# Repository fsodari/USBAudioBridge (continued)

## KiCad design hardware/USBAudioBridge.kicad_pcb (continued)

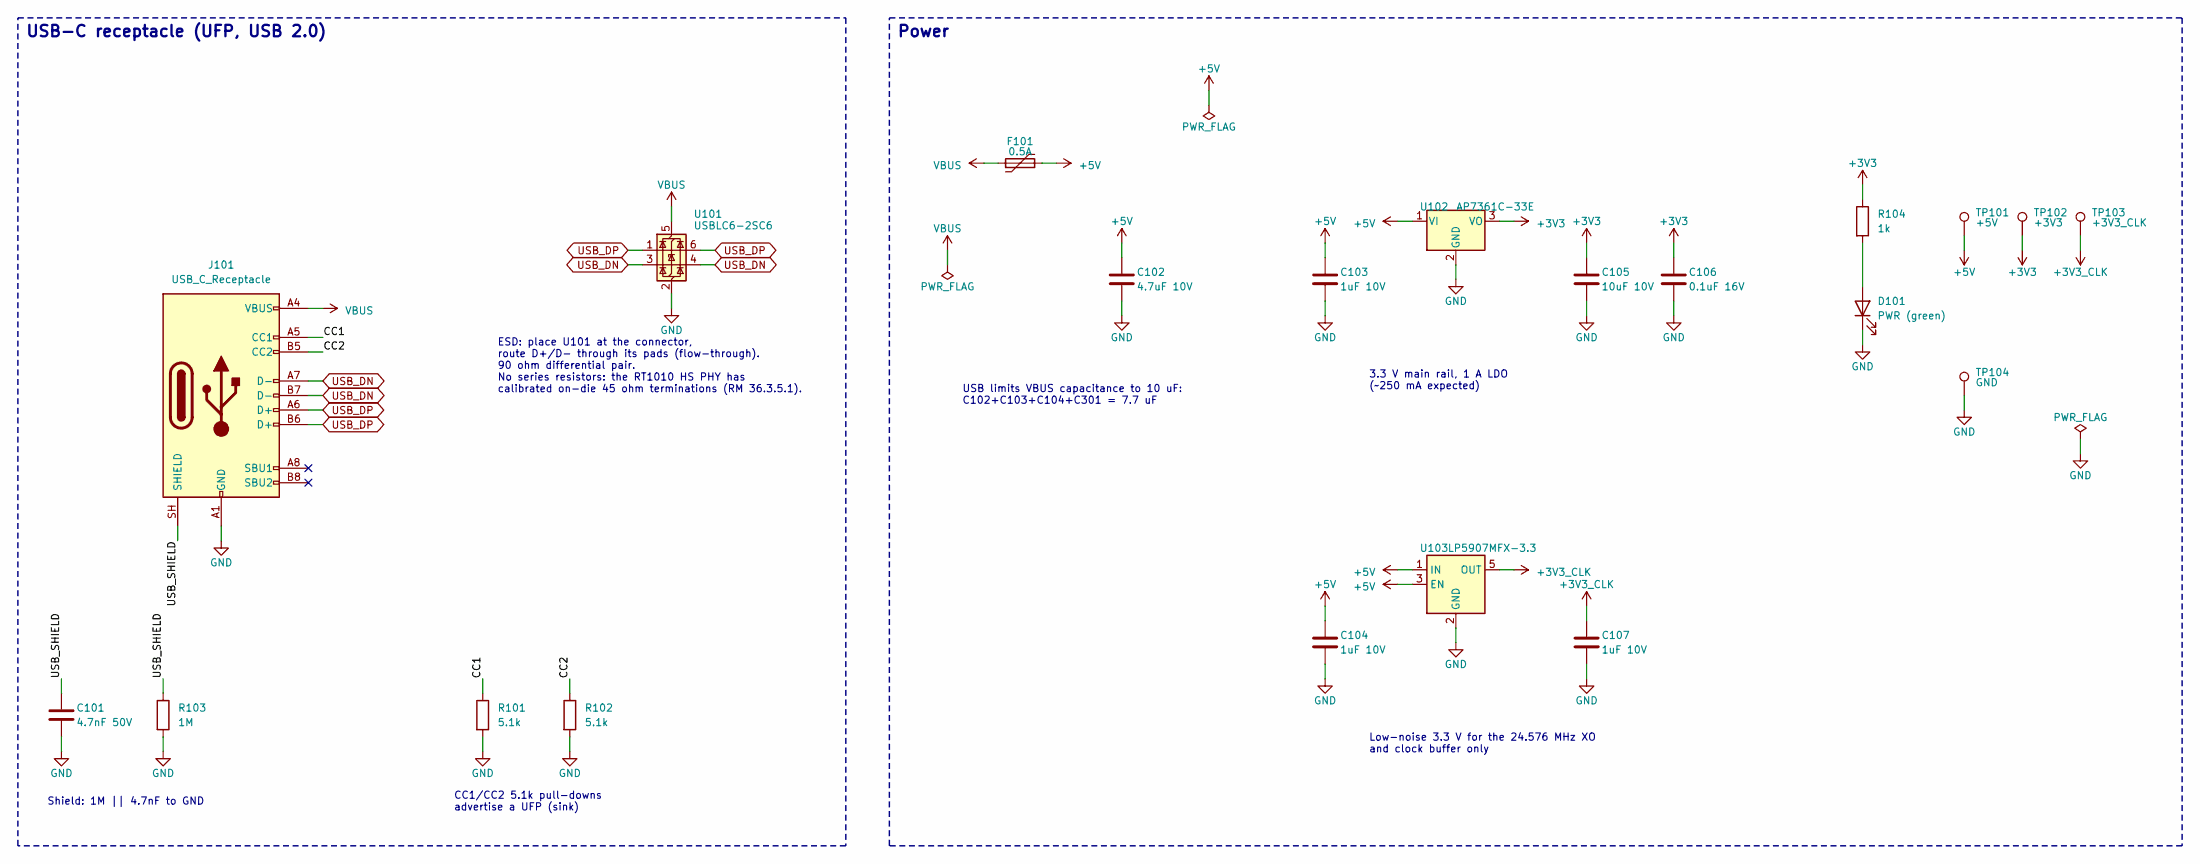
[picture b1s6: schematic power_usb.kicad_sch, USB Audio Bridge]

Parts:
C101: 4.7nF 50V; C_0402_1005Metric; MPN 0402B472K500NT; LCSC C1538
C102: 4.7uF 10V; C_0603_1608Metric; MPN CL10A475KO8NNNC; LCSC C19666
C103, C104, C107: 1uF 10V; C_0603_1608Metric; MPN CL10A105KB8NNNC; LCSC C15849
C105: 10uF 10V; C_0603_1608Metric; MPN CL10A106KP8NNNC; LCSC C19702
C106: 0.1uF 16V; C_0402_1005Metric; MPN CL05B104KO5NNNC; LCSC C1525
D101: PWR (green); LED_0603_1608Metric; MPN KT-0603YG; LCSC C2289
F101: 0.5A; Fuse_1206_3216Metric; MPN SMD1206P050TF/13.2; LCSC C43379
J101: USB_C_Receptacle; USB_C_Receptacle_GCT_USB4105-xx-A_16P_TopMnt_Horizontal; MPN USB4105-GF-A-120; LCSC C5184243
R101, R102: 5.1k; R_0402_1005Metric; MPN 0402WGF5101TCE; LCSC C25905
R103: 1M; R_0402_1005Metric; MPN 0402WGF1004TCE; LCSC C26083
R104: 1k; R_0402_1005Metric; MPN 0402WGF1001TCE; LCSC C11702
TP101: +5V; TestPoint_Pad_D1.0mm
TP102: +3V3; TestPoint_Pad_D1.0mm
TP103: +3V3_CLK; TestPoint_Pad_D1.0mm
TP104: GND; TestPoint_Pad_D1.0mm
U101: USBLC6-2SC6; SOT-23-6; MPN USBLC6-2SC6; LCSC C7519
U102: AP7361C-33E; SOT-223-3_TabPin2; MPN AP7361C-33E-13; LCSC C500795
U103: LP5907MFX-3.3; SOT-23-5; MPN LP5907MFX-3.3/NOPB; LCSC C80670

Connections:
+3V3: C105.1, C106.1, R104.1, TP102.1, U102.3 (VO); also elsewhere on the board
+3V3_CLK: C107.1, TP103.1, U103.5 (OUT); also elsewhere on the board
+5V: C102.1, C103.1, C104.1, F101.2, TP101.1, U102.1 (VI), U103.1 (IN), U103.3 (EN); also elsewhere on the board
/USB-C & Power/CC1: J101.A5 (CC1), R101.1
/USB-C & Power/CC2: J101.B5 (CC2), R102.1
/USB-C & Power/USB_SHIELD: C101.1, J101.SH (SHIELD), R103.1
GND: C101.2, C102.2, C103.2, C104.2, C105.2, C106.2, C107.2, D101.1 (K), J101.A1 (GND), J101.A12 (GND), J101.B1 (GND), J101.B12 (GND), R101.2, R102.2, R103.2, TP104.1, U101.2 (GND), U102.2 (GND), U103.2 (GND); also elsewhere on the board
unnamed: D101.2 (A), R104.2
USB_DN: J101.A7 (D-), J101.B7 (D-), U101.3 (I/O2), U101.4 (I/O2); also elsewhere on the board
USB_DP: J101.A6 (D+), J101.B6 (D+), U101.1 (I/O1), U101.6 (I/O1); also elsewhere on the board
VBUS: F101.1, J101.A4 (VBUS), J101.A9 (VBUS), J101.B4 (VBUS), J101.B9 (VBUS), U101.5 (VBUS)

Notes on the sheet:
Low-noise 3.3 V for the 24.576 MHz XO and clock buffer only
CC1/CC2 5.1k pull-downs advertise a UFP (sink)
USB-C receptacle (UFP, USB 2.0)
Power
Shield: 1M || 4.7nF to GND
3.3 V main rail, 1 A LDO (~250 mA expected)
USB limits VBUS capacitance to 10 uF: C102+C103+C104+C301 = 7.7 uF
ESD: place U101 at the connector, route D+/D- through its pads (flow-through). 90 ohm differential pair. No series resistors: the RT1010 HS PHY has calibrated on-die 45 ohm terminations (RM 36.3.5.1).

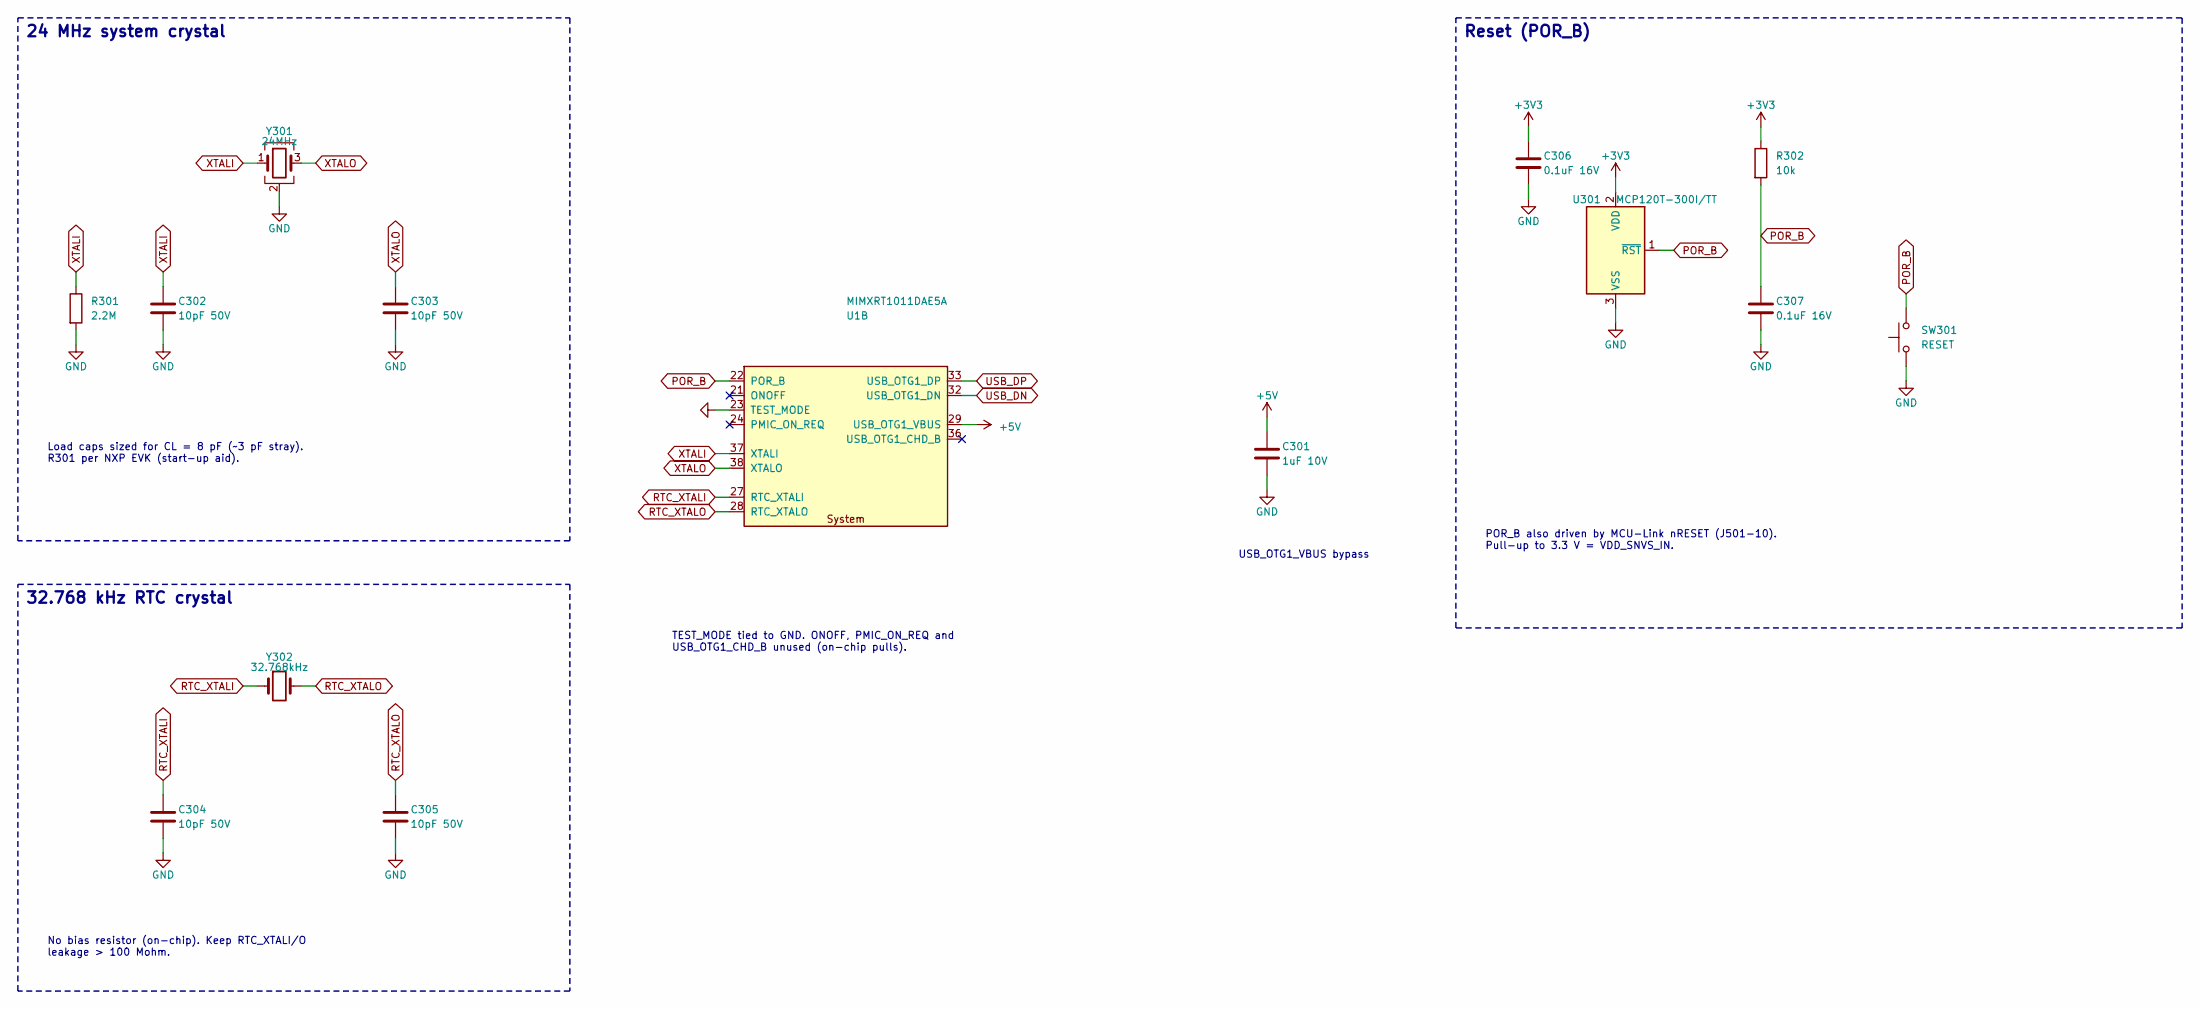
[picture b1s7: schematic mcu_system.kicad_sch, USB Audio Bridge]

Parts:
C301: 1uF 10V; C_0603_1608Metric; MPN CL10A105KB8NNNC; LCSC C15849
C302, C303, C304, C305: 10pF 50V; C_0402_1005Metric; MPN CL05C100JB5NNNC; LCSC C32949
C306, C307: 0.1uF 16V; C_0402_1005Metric; MPN CL05B104KO5NNNC; LCSC C1525
R301: 2.2M; R_0402_1005Metric; MPN 0402WGF2204TCE; LCSC C11490
R302: 10k; R_0402_1005Metric; MPN 0402WGF1002TCE; LCSC C25744
SW301: RESET; SW_SPST_PTS810; MPN PTS810SJG250SMTRLFS; LCSC C221895
U1: MIMXRT1011DAE5A; LQFP-80_12x12mm_P0.5mm; MPN MIMXRT1011DAE5A; LCSC C1575810
U301: MCP120T-300I/TT; SOT-23; MPN MCP120T-300I/TT; LCSC C625180
Y301: 24MHz; Crystal_SMD_3225-4Pin_3.2x2.5mm; MPN 3225-24-8-10-10/A; LCSC C2981672
Y302: 32.768kHz; Crystal_SMD_3215-2Pin_3.2x1.5mm; MPN Q13FC13500002; LCSC C48615

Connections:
+3V3: C306.1, R302.1, U301.2 (VDD); also elsewhere on the board
+5V: C301.1, U1.29 (USB_OTG1_VBUS); also elsewhere on the board
GND: C301.2, C302.2, C303.2, C304.2, C305.2, C306.2, C307.2, R301.2, SW301.1, U1.23 (TEST_MODE), U301.3 (VSS), Y301.2 (G), Y301.4 (G); also elsewhere on the board
POR_B: C307.1, R302.2, SW301.2, U1.22 (POR_B), U301.1 (~RST); also elsewhere on the board
RTC_XTALI: C304.1, U1.27 (RTC_XTALI), Y302.1
RTC_XTALO: C305.1, U1.28 (RTC_XTALO), Y302.2
USB_DN: U1.32 (USB_OTG1_DN); also elsewhere on the board
USB_DP: U1.33 (USB_OTG1_DP); also elsewhere on the board
XTALI: C302.1, R301.1, U1.37 (XTALI), Y301.1
XTALO: C303.1, U1.38 (XTALO), Y301.3

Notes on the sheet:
POR_B also driven by MCU-Link nRESET (J501-10). Pull-up to 3.3 V = VDD_SNVS_IN.
24 MHz system crystal
TEST_MODE tied to GND. ONOFF, PMIC_ON_REQ and USB_OTG1_CHD_B unused (on-chip pulls).
USB_OTG1_VBUS bypass
32.768 kHz RTC crystal
Reset (POR_B)
No bias resistor (on-chip). Keep RTC_XTALI/O leakage > 100 Mohm.
Load caps sized for CL = 8 pF (~3 pF stray). R301 per NXP EVK (start-up aid).

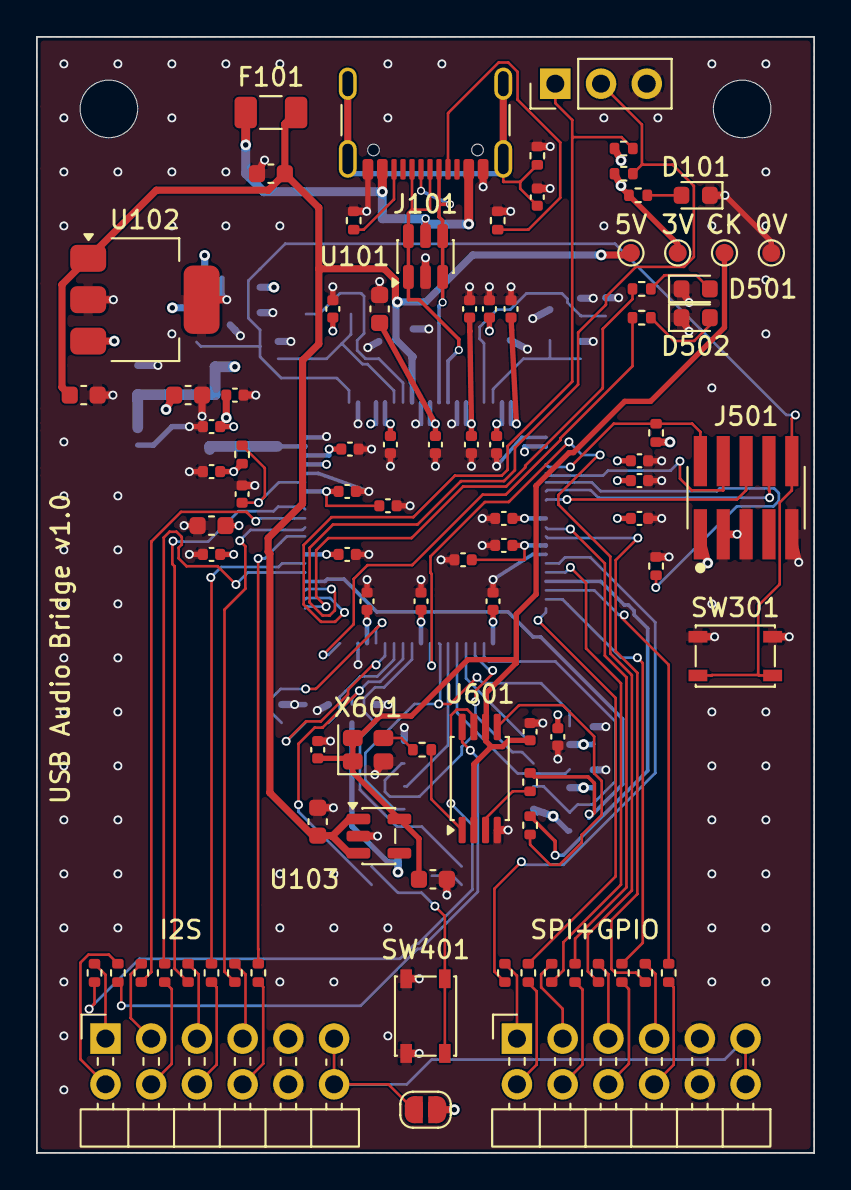
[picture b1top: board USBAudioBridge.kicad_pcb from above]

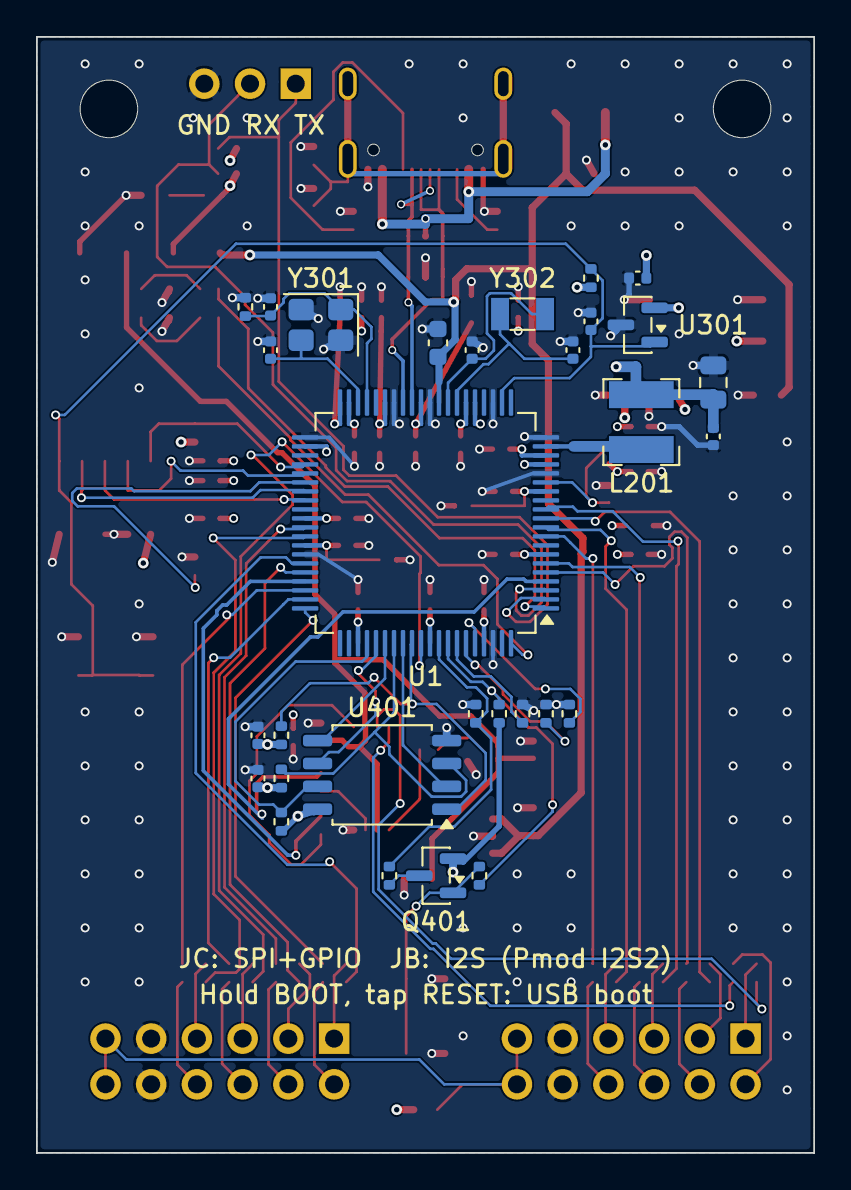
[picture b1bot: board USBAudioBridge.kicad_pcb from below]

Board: 4 copper layers, 43.2 x 62.0 mm, 120 parts (30 on the bottom side), 86 nets.

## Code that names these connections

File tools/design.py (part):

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    for n in ["USB_DP", "USB_DN", "POR_B", "MCLK_SAI", "MCLK_GPT",
              "I2S_TX_BCLK", "I2S_TX_LRCLK", "I2S_TX_DATA", "I2S_RX_BCLK", "I2S_RX_LRCLK",
              "I2S_RX_DATA", "SPI_CS", "SPI_MOSI", "SPI_MISO", "SPI_SCK",
              "PMOD_INT", "PMOD_RST", "PMOD_GPIO0", "PMOD_GPIO1"]:
        g[n] = "bidirectional"
    d.globals = g

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        "RT1010 audio, bottom row (7-10) MCLK/LRCK/SCLK/SDOUT carries RT1010 -> FPGA audio.\n"
        "Boot: BOOT_MODE[1:0]=10 (internal boot, FlexSPI-A QSPI NOR) by default. Hold BOOT and "
        "press RESET for 01 (serial downloader over USB).\n"
        "Debug: MCU-Link 10-pin Cortex debug header (SWD + SWO), 3-pin LPUART1 console header.\n"
        "\n"
        "PIN MAP\n"
        "  GPIO_01..03  SAI1 RX BCLK/SYNC/DATA0   (I2S input bus, FPGA -> RT1010)\n"
        "  GPIO_04,06,07 SAI1 TX DATA0/BCLK/SYNC  (I2S output bus, RT1010 -> FPGA)\n"
        "  GPIO_08      SAI1_MCLK in              GPIO_00, 05, 13, AD_08, AD_14  spare (NC)\n"
        "  GPIO_09/10   LPUART1 RX/TX             GPIO_11/12  LED1/LED2\n"
        "  GPIO_AD_04/05/06 LPSPI1 SDO/PCS0/SCK   GPIO_SD_05  LPSPI1 SDI (daisy select 1)\n"
        "  GPIO_AD_00 PMOD_INT, AD_07 PMOD_RST, AD_01/02 PMOD_GPIO0/1 (LPI2C2 or LPUART4 capable)\n"
        "  GPIO_AD_09..13 SWO/TDI/JTAG_MOD/SWCLK/SWDIO\n"
        "  GPIO_SD_06..11 FlexSPI-A QSPI flash    GPIO_SD_00..04 BT_CFG / BOOT_MODE straps"
    )
    sh.text(notes, (30.48, 152.4), size=1.6)
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               "9": "I2S_TX_DATA", "8": "NC", "6": "I2S_TX_BCLK", "5": "I2S_TX_LRCLK",
               "4": "MCLK_SAI", "3": "UART_RX", "2": "UART_TX", "1": "LED1", "80": "LED2",
               "79": "NC",
               "60": "PMOD_INT", "59": "PMOD_GPIO0", "58": "PMOD_GPIO1", "57": "MCLK_GPT",
               "56": "SPI_MOSI", "55": "SPI_CS", "52": "SPI_SCK", "51": "PMOD_RST",
               "49": "NC", "48": "SWO", "47": "JTAG_TDI", "46": "JTAG_MOD", "45": "SWCLK",
               "44": "SWDIO", "43": "NC"})
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    sh.link("CLK_BUF_IN", (r601, "2"), (b, "1"), label=False)
    cap(sh, "C602", "0.1uF 16V", (106.68, 50.8), "+3V3_CLK")
    # buffer output -> series resistor; the turn columns keep the four routes from crossing
    for ref, pin, y_r, mid, net in (("R602", "3", 58.42, 149.86, "MCLK_SAI"),
                                    ("R603", "5", 68.58, None, "MCLK_GPT"),
                                    ("R604", "7", 78.74, 149.86, "JB_RX_MCLK"),
                                    ("R605", "8", 88.9, 144.78, "JB_TX_MCLK")):
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                fields=PMOD_FIELDS)
    jc.connect({"1": "JC_SPI_CS", "2": "JC_SPI_MOSI", "3": "JC_SPI_MISO", "4": "JC_SPI_SCK",
                "5": "GND", "6": "PMOD_VCC", "7": "JC_INT", "8": "JC_RST",
                "9": "JC_GPIO0", "10": "JC_GPIO1", "11": "GND", "12": "PMOD_VCC"})
    left = [("R612", "SPI_CS", "JC_SPI_CS"), ("R613", "SPI_MOSI", "JC_SPI_MOSI"),
            ("R614", "SPI_MISO", "JC_SPI_MISO"), ("R615", "SPI_SCK", "JC_SPI_SCK")]
    right = [("R616", "JC_INT", "PMOD_INT"), ("R617", "JC_RST", "PMOD_RST"),
             ("R618", "JC_GPIO0", "PMOD_GPIO0"), ("R619", "JC_GPIO1", "PMOD_GPIO1")]
    for i, (ref, a, b_) in enumerate(left):
        res(sh, ref, "33", (248.92, 167.64 + i * 10.16), a, b_, horizontal=True)
    for i, (ref, a, b_) in enumerate(right):
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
